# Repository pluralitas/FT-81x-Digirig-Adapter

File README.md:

# FT-81x-Digirig-Adapter
Low profile Digirig Mobile adapter for FT-81x based on design by [BG6LH](https://github.com/BG6LH)

I bought the Digirig mobile and had to interface it with my Yaesu FT817 but neither want to buy the expensively priced cables nor like that it protrudes out the rear. I was unable to find any right angle mini-DIN but luckily i came across BG8LH's [FT-81x Bluetooth digirig adapter](https://github.com/BG6LH/FT-81x-BT-DIGI-Adaptor). I downloaded his github and proceed to mod it, ripping up everything but the mini-DINs and then added 2x 3.5mm TRRS jacks.

## Bill of materials (BOM)
- 1x PJ320D (Green)
- 1x PJ320D (Black)
- 1x Mini-DIN-6PR
- 1x Mini-DIN-8PR

## Pictures

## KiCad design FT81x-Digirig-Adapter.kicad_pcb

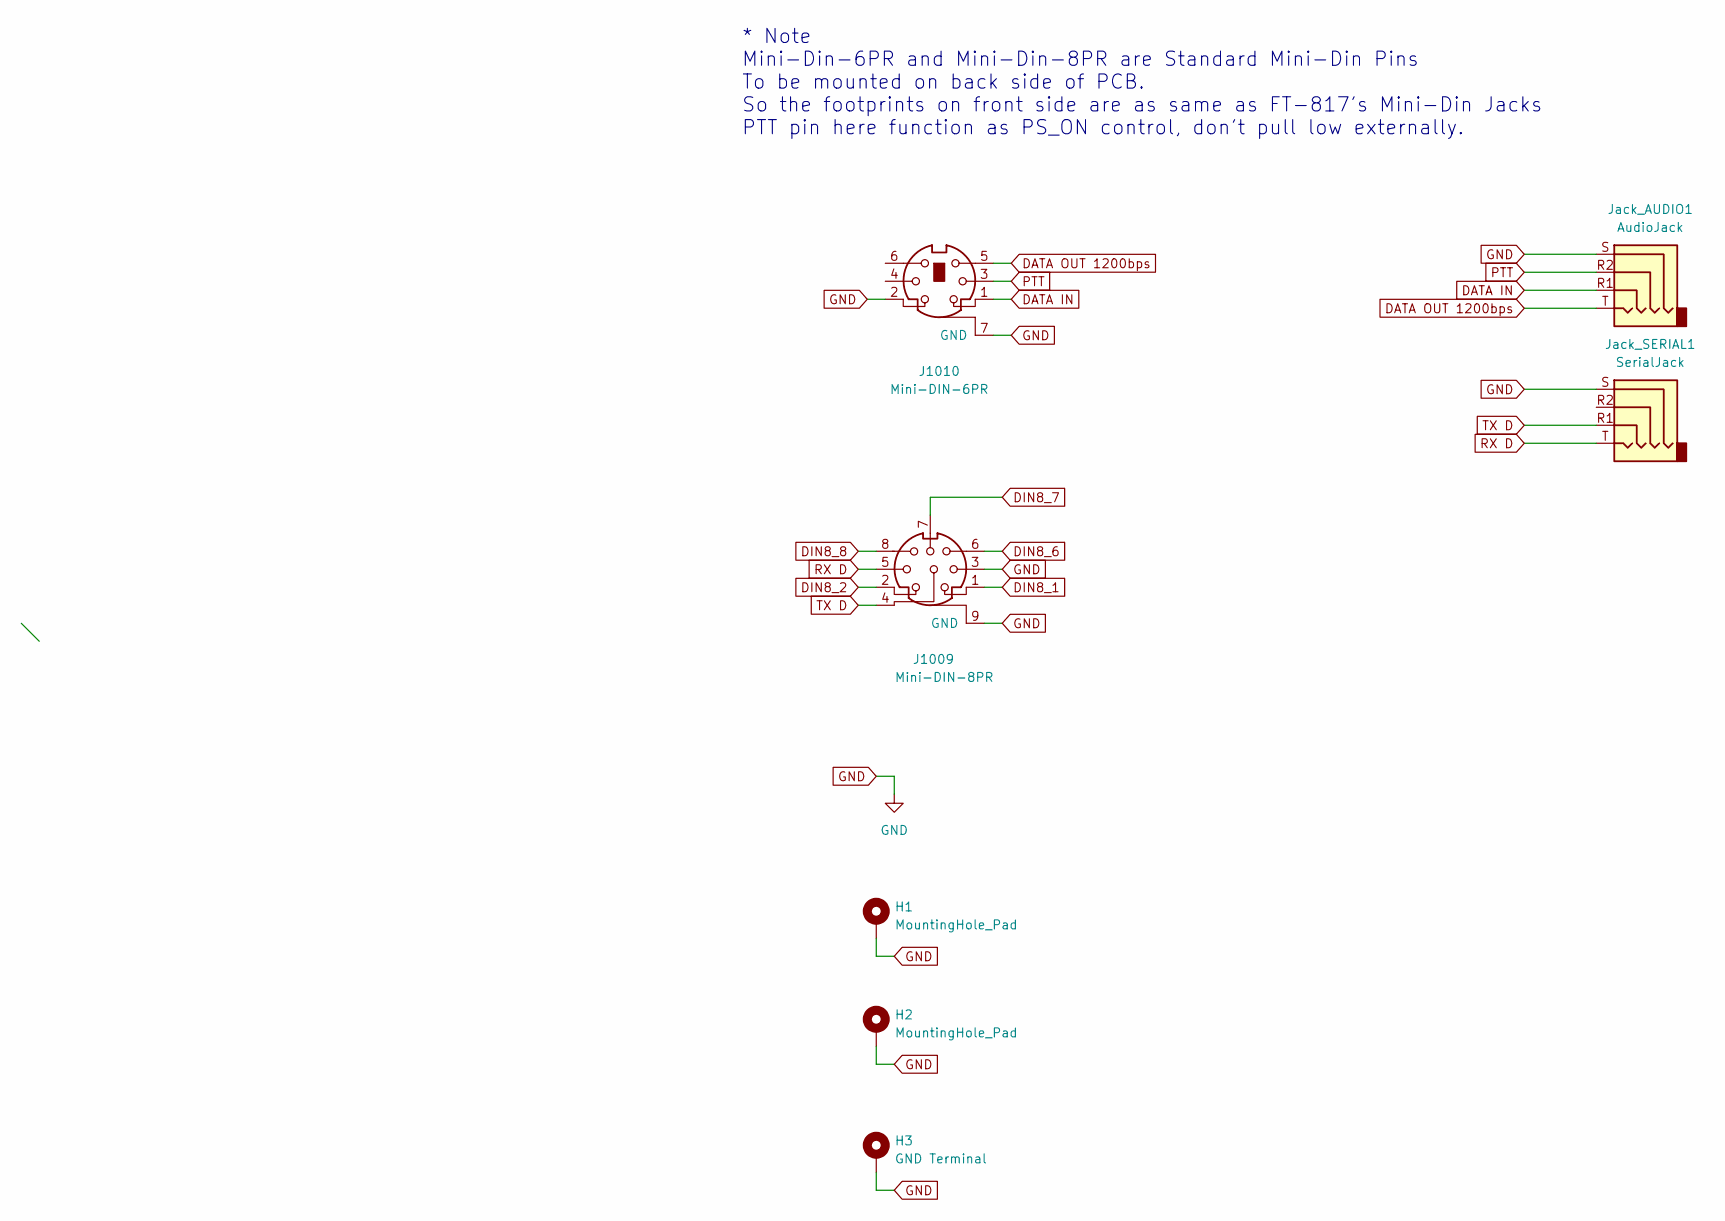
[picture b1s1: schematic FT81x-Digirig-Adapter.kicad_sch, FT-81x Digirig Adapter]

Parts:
H1, H2: MountingHole_Pad; MountingHole_2.7mm_M2.5_DIN965_Pad_TopOnly
H3: GND Terminal; FT-817_GND_terminal_8.4mm_M8_Pad_TopBottom
J1009: Mini-DIN-8PR; MD-8Pin_Reverse
J1010: Mini-DIN-6PR; MD-6Pin_Reverse
Jack_AUDIO1: AudioJack; Jack_3.5mm_PJ320D_Horizontal
Jack_SERIAL1: SerialJack; Jack_3.5mm_PJ320D_Horizontal

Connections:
DATA IN: J1010.1, Jack_AUDIO1.R1
DATA OUT 1200bps: J1010.5, Jack_AUDIO1.T
DIN8_1: J1009.1
DIN8_2: J1009.2
DIN8_6: J1009.6
DIN8_7: J1009.7
DIN8_8: J1009.8
GND: H1.1, H2.1, H3.1, J1009.3, J1009.9 (GND), J1010.2, J1010.7 (GND), Jack_AUDIO1.S, Jack_SERIAL1.S
PTT: J1010.3, Jack_AUDIO1.R2
RX D: J1009.5, Jack_SERIAL1.T
TX D: J1009.4, Jack_SERIAL1.R1

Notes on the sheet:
* Note Mini-Din-6PR and Mini-Din-8PR are Standard Mini-Din Pins To be mounted on back side of PCB. So the footprints on front side are as same as FT-817's Mini-Din Jacks PTT pin here function as PS_ON control, don't pull low externally.

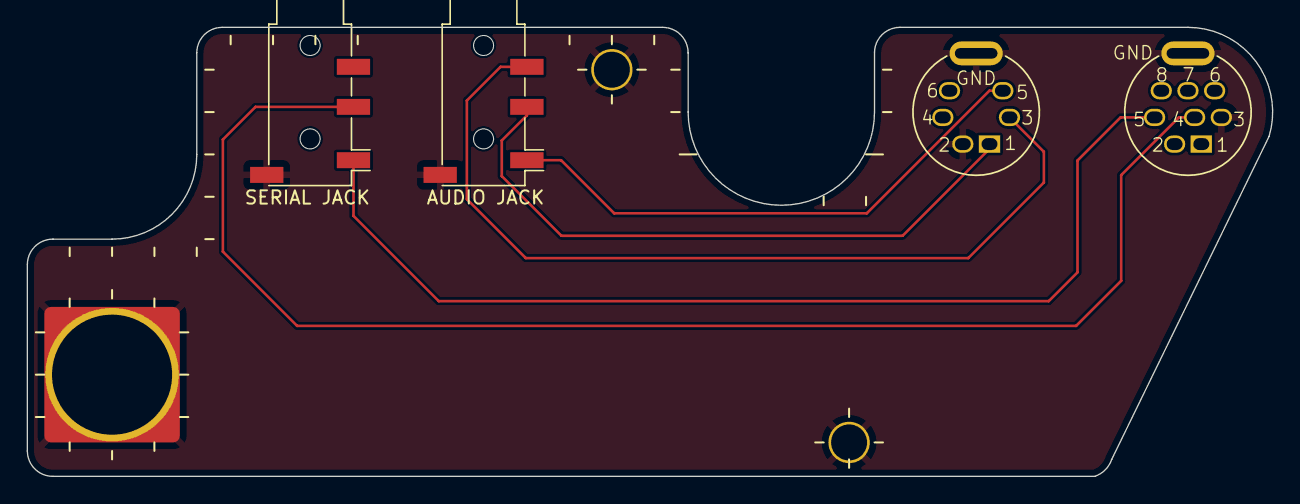
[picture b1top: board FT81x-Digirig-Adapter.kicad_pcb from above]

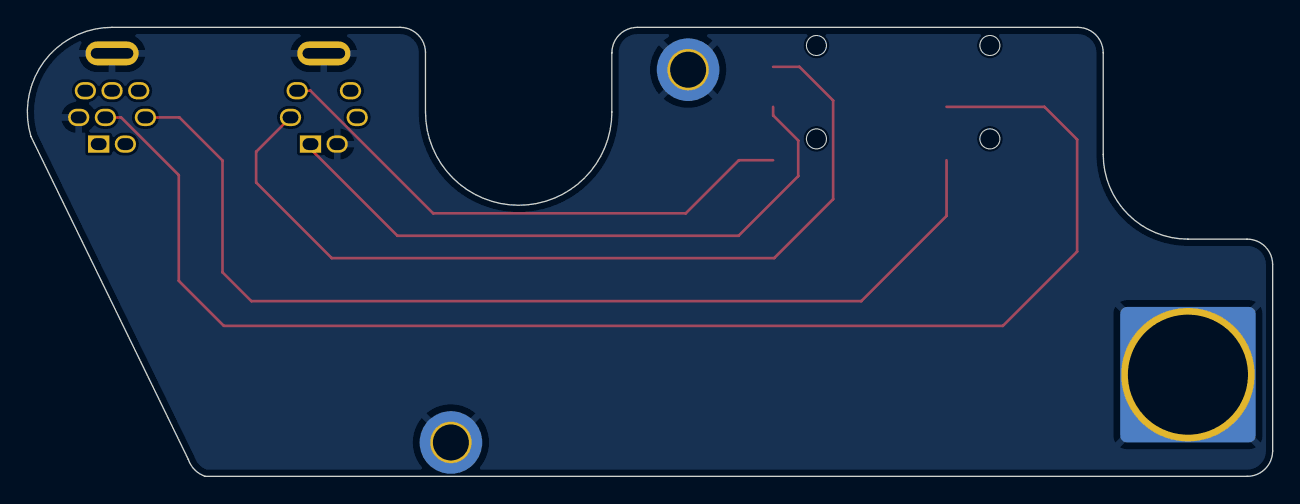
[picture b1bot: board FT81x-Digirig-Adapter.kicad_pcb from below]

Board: 2 copper layers, 93.3 x 33.7 mm, 7 parts (2 on the bottom side), 6 nets.

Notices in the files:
FT81x-Digirig-Adapter.kicad_pcb:
CC-BY-NC-SA 4.0
